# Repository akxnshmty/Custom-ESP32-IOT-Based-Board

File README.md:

# Custom-ESP32-IOT-Based-Board
Custom Multi-Sensor IoT Board with SD Card, Flash Memory, Microphone & High-Speed Routing

This project is a fully custom 4-layer IoT development board built around the ESP32, integrating multiple peripherals such as an SD card interface, external flash memory, I²C sensors, and an onboard microphone. It is designed as a compact, enclosure-ready hardware platform suitable for embedded, IoT, and data-logging applications.

⸻

🚀 Features
	•	ESP32-WROOM based core controller
	•	SD Card interface for data logging
	•	Flash memory IC for additional storage
	•	On-board microphone for audio input
	•	I²C sensor interface for environmental/IMU sensors
	•	User GPIO headers for expansion
	•	4-layer PCB with dedicated ground and power planes
	•	Mounting holes for enclosure integration
	•	Custom 3D models for accurate visualization
	•	Manual routing (0% autorouter) for full design control

⸻

🧩 Hardware Overview

4-Layer Stackup
	•	Layer 1 (Top): Components + High-speed signal routing
	•	Layer 2: Solid GND plane for low-noise return paths
	•	Layer 3: Power plane (5V + 3.3V distribution)
	•	Layer 4 (Bottom): Signal routing + copper zones

This architecture improves signal integrity, noise immunity, and routing efficiency, especially for the SD card, flash memory, and microphone circuits.

⸻

🔧 Key Technical Highlights

Manual Routing
	•	Differential pair routing
	•	Length matching for timing-critical nets
	•	I²C bus routing for sensors
	•	High-speed clock lines
	•	Optimized power traces
	•	Dedicated copper zones for GND and power
	•	Via stitching for ground reinforcement

Design & Validation
	•	Full manual DRC debugging
	•	Fixed annular ring and clearance violations
	•	Added test points, accessible GPIO, and labeled connectors
	•	Optimized analog routing for microphone stage

Mechanical Integration
	•	Exported STEP and WRL models
	•	Assembled 3D view for enclosure planning
	•	Added mounting holes
	•	Custom silkscreen signature

Firmware (Coming Soon)
	•	SD card logging demo
	•	Sensor reading script (I²C)
	•	Microphone input test
	•	Wi-Fi provisioning & OTA updates

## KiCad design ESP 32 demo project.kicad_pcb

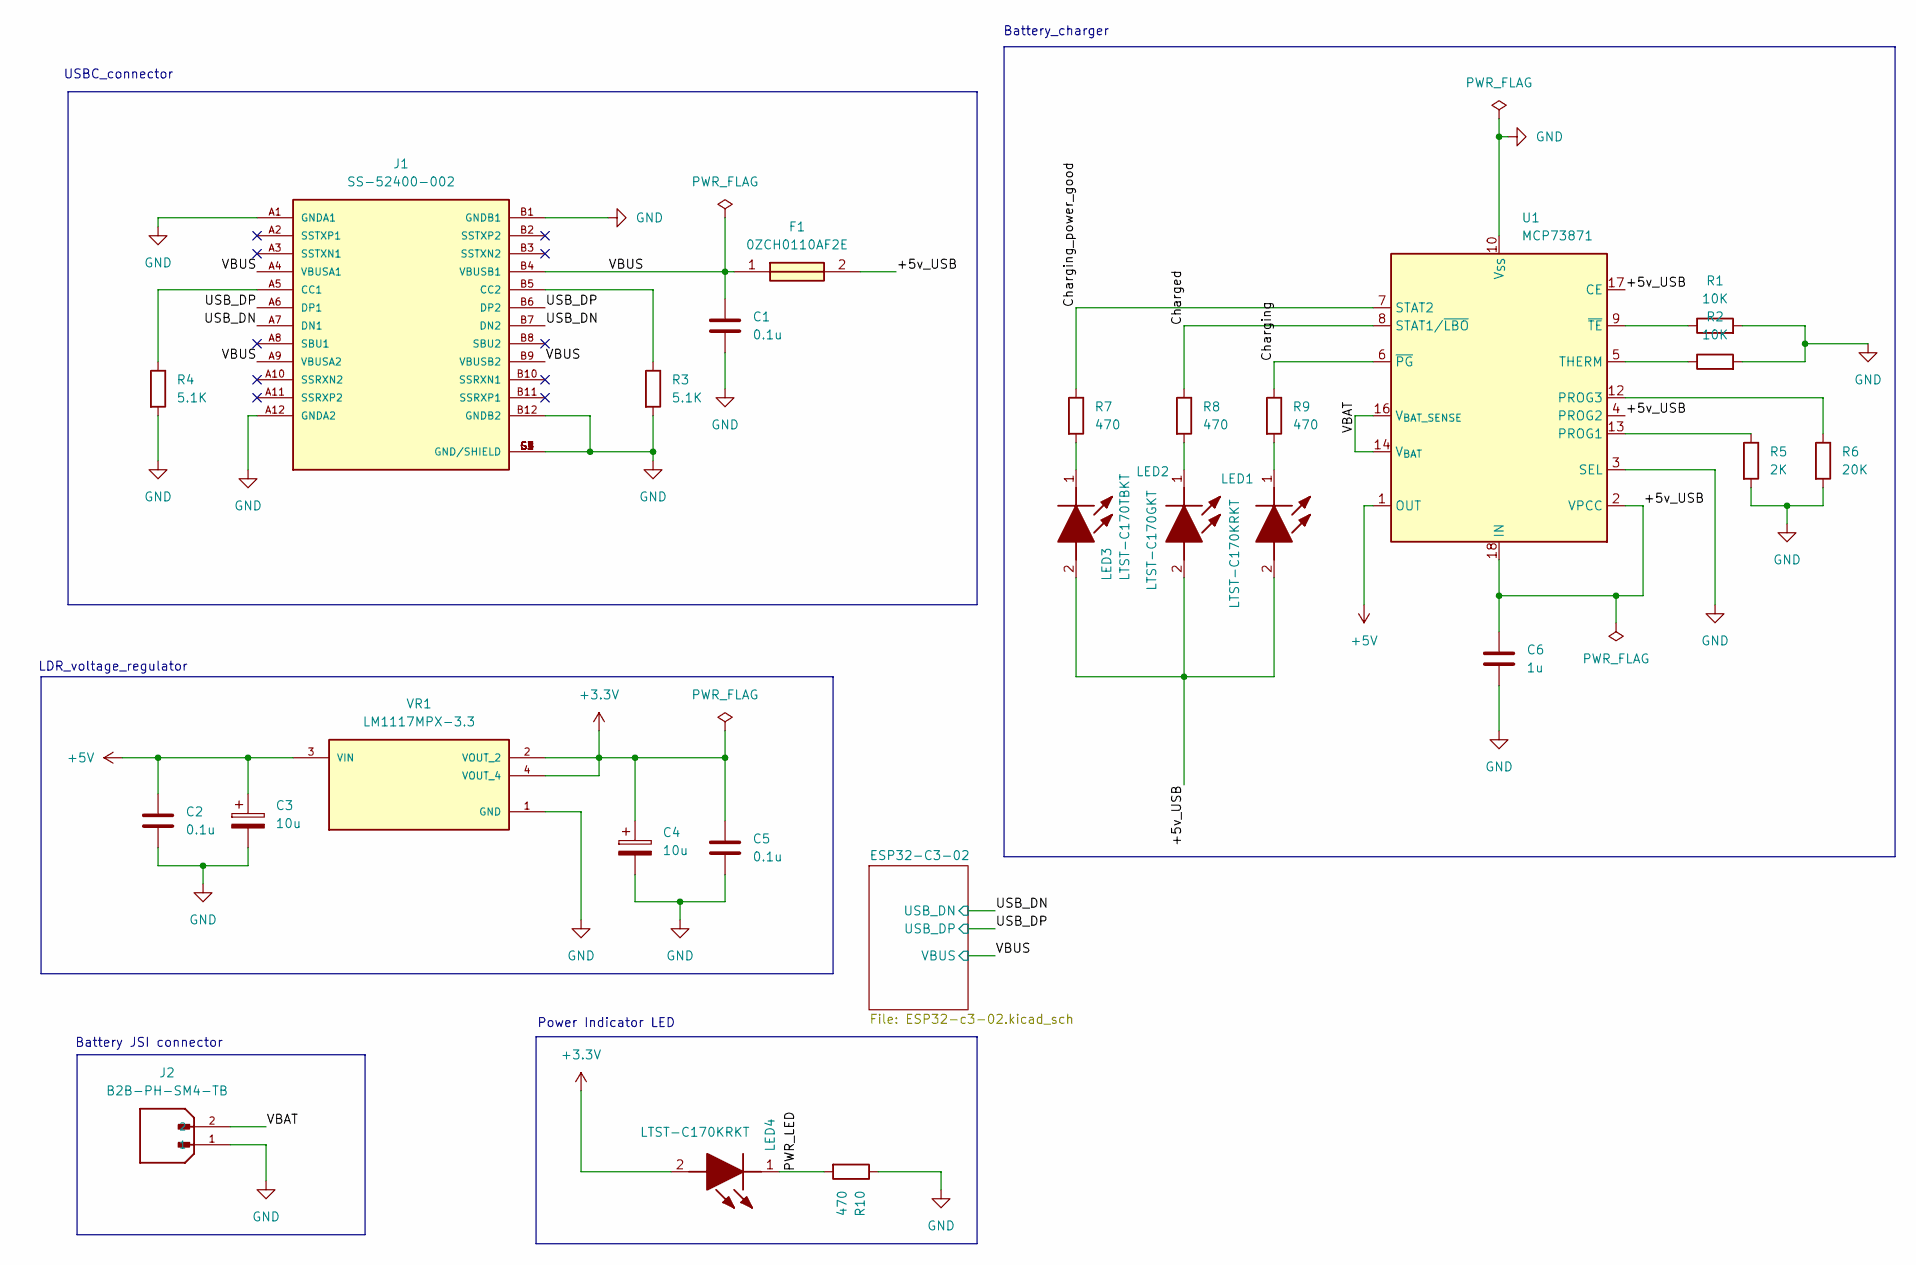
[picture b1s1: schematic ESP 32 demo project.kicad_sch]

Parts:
C1, C2, C5: 0.1u; C_0805_2012Metric
C3, C4: 10u; T491A
C6: 1u; C_0805_2012Metric
F1: 0ZCH0110AF2E; FUSC3226X100N; Manufacturer_Part_Number 0ZCH0110AF2E
J1: SS-52400-002; BELFUSE_SS-52400-002; PARTREV A0
J2: B2B-PH-SM4-TB; JST_B2B-PH-SM4-TB; PARTREV N/A
LED1, LED4: LTST-C170KRKT; LEDC2012X120N; Manufacturer_Part_Number LTST-C170KRKT; Mouser Part Number 859-LTST-C170KRKT
LED2: LTST-C170GKT; LEDC2012X120N; Manufacturer_Part_Number LTST-C170GKT; Mouser Part Number 859-LTST-C170GKT
LED3: LTST-C170TBKT; LEDC2012X120N; Manufacturer_Part_Number LTST-C170TBKT; Mouser Part Number 859-LTST-C170TBKT
R1, R2: 10K; R_0805_2012Metric
R3, R4: 5.1K; R_0805_2012Metric
R5: 2K; R_0805_2012Metric
R6: 20K; R_0805_2012Metric
R7, R8, R9, R10: 470; R_0805_2012Metric
U1: MCP73871; QFN-20-1EP_4x4mm_P0.5mm_EP2.5x2.5mm
VR1: LM1117MPX-3.3; VREG_LM1117MPX-3.3

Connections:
+3.3V: C4.1, C5.1, LED4.2 (A), VR1.2 (VOUT_2), VR1.4 (VOUT_4); also elsewhere on the board
/Charged: R8.1, U1.8 (STAT1/~LBO)
/Charging: R9.1, U1.6 (~PG)
/Charging_power_good: R7.1, U1.7 (STAT2)
/PWR_LED: LED4.1 (K), R10.2; also elsewhere on the board
/USB_DN: J1.A7 (DN1), J1.B7 (DN2); also elsewhere on the board
/USB_DP: J1.A6 (DP1), J1.B6 (DP2); also elsewhere on the board
/VBAT: J2.2, U1.14 (V_{BAT}), U1.15 (V_{BAT}), U1.16 (V_{BAT_SENSE})
/VBUS: C1.1, F1.1, J1.A4 (VBUSA1), J1.A9 (VBUSA2), J1.B4 (VBUSB1), J1.B9 (VBUSB2); also elsewhere on the board
unnamed: J1.A5 (CC1), R4.1
unnamed: J1.B5 (CC2), R3.1
unnamed: LED1.1 (K), R9.2
unnamed: LED2.1 (K), R8.2
unnamed: LED3.1 (K), R7.2
unnamed: R5.1, U1.13 (PROG1)
unnamed: R6.1, U1.12 (PROG3)
unnamed: R2.1, U1.5 (THERM)
unnamed: R1.1, U1.9 (~TE)

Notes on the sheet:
Battery JSI connector
Power Indicator LED
LDR_voltage_regulator
Battery_charger
USBC_connector

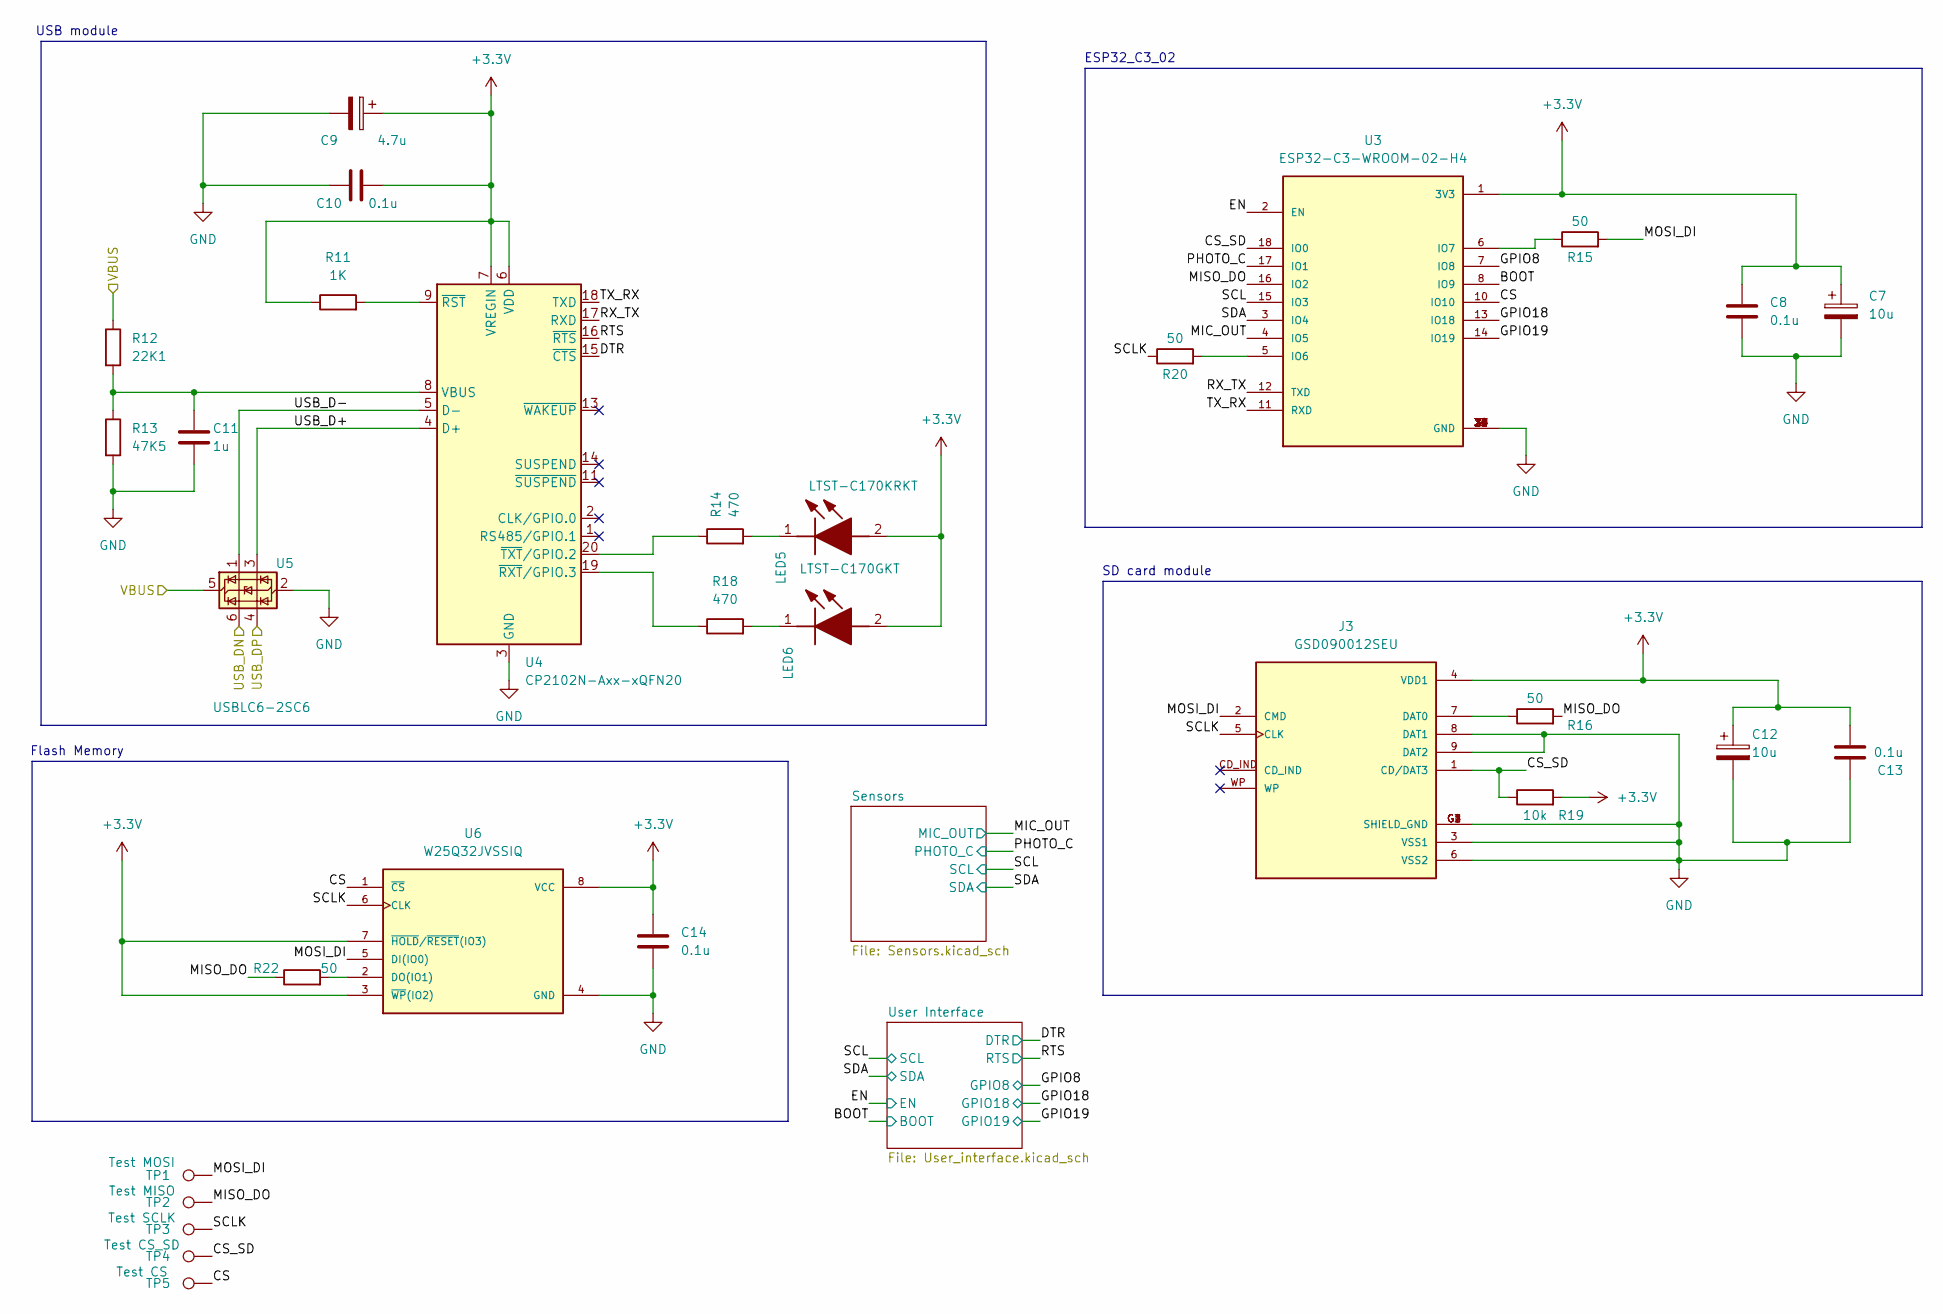
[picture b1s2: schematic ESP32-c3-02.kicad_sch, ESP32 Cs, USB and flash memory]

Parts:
C7, C12: 10u; T491A
C8, C10, C13, C14: 0.1u; C_0805_2012Metric
C9: 4.7u; T491A
C11: 1u; C_0805_2012Metric
J3: GSD090012SEU; AMPHENOL_GSD090012SEU; PARTREV E
LED5: LTST-C170GKT; LEDC2012X120N; Manufacturer_Part_Number LTST-C170GKT; Mouser Part Number 859-LTST-C170GKT
LED6: LTST-C170KRKT; LEDC2012X120N; Manufacturer_Part_Number LTST-C170KRKT; Mouser Part Number 859-LTST-C170KRKT
R11: 1K; R_0805_2012Metric
R12: 22K1; R_0805_2012Metric
R13: 47K5; R_0805_2012Metric
R14, R18: 470; R_0805_2012Metric
R15, R16, R20, R22: 50; R_0805_2012Metric
R19: 10k; R_0805_2012Metric
TP1: Test MOSI; TestPoint_Pad_D1.0mm
TP2: Test MISO; TestPoint_Pad_D1.0mm
TP3: Test SCLK; TestPoint_Pad_D1.0mm
TP4: Test CS_SD; TestPoint_Pad_D1.0mm
TP5: Test CS; TestPoint_Pad_D1.0mm
U3: ESP32-C3-WROOM-02-H4; MODULE_ESP32-C3-WROOM-02-H4
U4: CP2102N-Axx-xQFN20; SiliconLabs_QFN-20-1EP_3x3mm_P0.5mm_EP1.8x1.8mm
U5: USBLC6-2SC6; SOT-23-6
U6: W25Q32JVSSIQ; SOIC127P790X216-8N; M_PART_NUMBER W25QXX

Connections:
+3.3V: C7.1, C8.1, C9.1, C10.1, C12.1, C13.2, C14.1, J3.4 (VDD1), LED5.2 (A), LED6.2 (A), R11.1, R19.2, U3.1 (3V3), U4.6 (VDD), U4.7 (VREGIN), U6.3 (~WP(IO2)), U6.7 (~HOLD/~RESET(IO3)), U6.8 (VCC); also elsewhere on the board
/ESP32-C3-02/BOOT: U3.8 (IO9); also elsewhere on the board
/ESP32-C3-02/CS: TP5.1, U3.10 (IO10), U6.1 (~CS)
/ESP32-C3-02/CS_SD: J3.1 (CD/DAT3), R19.1, TP4.1, U3.18 (IO0)
/ESP32-C3-02/DTR: U4.15 (~CTS); also elsewhere on the board
/ESP32-C3-02/EN: U3.2 (EN); also elsewhere on the board
/ESP32-C3-02/GPIO8: U3.7 (IO8); also elsewhere on the board
/ESP32-C3-02/GPIO18: U3.13 (IO18); also elsewhere on the board
/ESP32-C3-02/GPIO19: U3.14 (IO19); also elsewhere on the board
/ESP32-C3-02/MIC_OUT: U3.4 (IO5); also elsewhere on the board
/ESP32-C3-02/MISO_DO: R16.2, R22.1, TP2.1, U3.16 (IO2)
/ESP32-C3-02/MOSI_DI: J3.2 (CMD), R15.2, TP1.1, U6.5 (DI(IO0))
/ESP32-C3-02/PHOTO_C: U3.17 (IO1); also elsewhere on the board
/ESP32-C3-02/RTS: U4.16 (~RTS); also elsewhere on the board
/ESP32-C3-02/RX_TX: U3.12 (TXD), U4.17 (RXD)
/ESP32-C3-02/SCL: U3.15 (IO3); also elsewhere on the board
/ESP32-C3-02/SCLK: J3.5 (CLK), R20.1, TP3.1, U6.6 (CLK)
/ESP32-C3-02/SDA: U3.3 (IO4); also elsewhere on the board
/ESP32-C3-02/TX_RX: U3.11 (RXD), U4.18 (TXD)
/ESP32-C3-02/USB_D+: U4.4 (D+), U5.3 (I/O2)
/ESP32-C3-02/USB_D-: U4.5 (D-), U5.1 (I/O1)
/USB_DN: U5.6 (I/O1); also elsewhere on the board
/USB_DP: U5.4 (I/O2); also elsewhere on the board
/VBUS: R12.1, U5.5 (VBUS); also elsewhere on the board
unnamed: J3.7 (DAT0), R16.1
unnamed: LED5.1 (K), R14.2
unnamed: LED6.1 (K), R18.2
unnamed: R20.2, U3.5 (IO6)
unnamed: R15.1, U3.6 (IO7)
unnamed: C11.1, R12.2, R13.1, U4.8 (VBUS)
unnamed: R11.2, U4.9 (~RST)
unnamed: R18.1, U4.19 (~RXT/GPIO.3)
unnamed: R14.1, U4.20 (~TXT/GPIO.2)
unnamed: R22.2, U6.2 (DO(IO1))

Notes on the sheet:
Flash Memory
ESP32_C3_02
SD card module
USB module

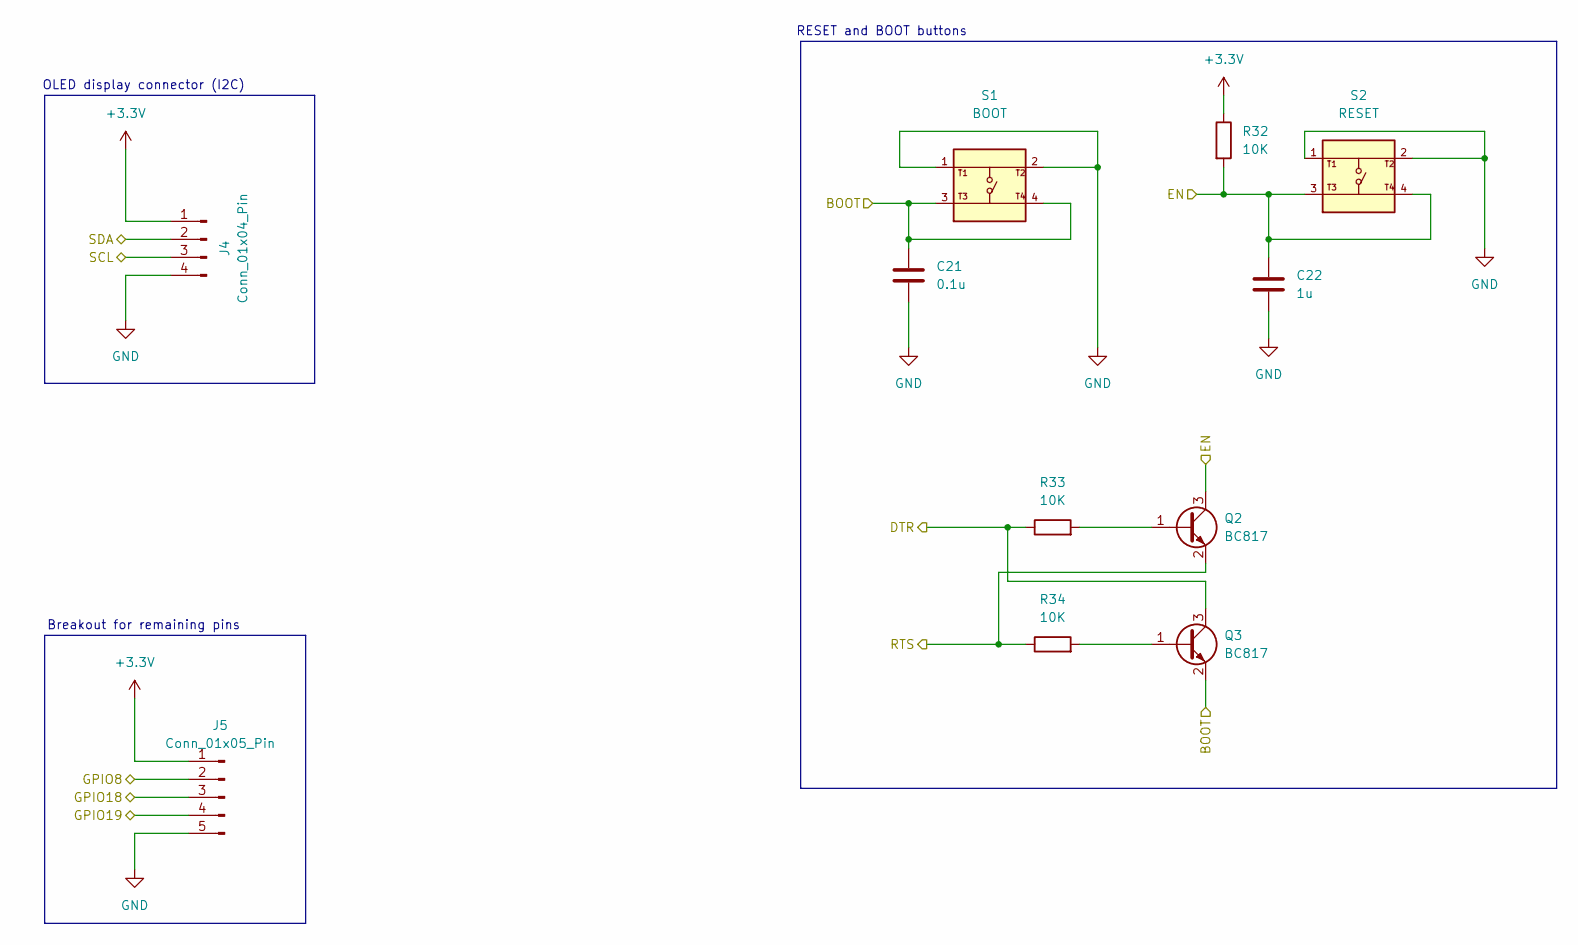
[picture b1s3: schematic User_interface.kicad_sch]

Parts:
C21: 0.1u; C_0805_2012Metric
C22: 1u; C_0805_2012Metric
J4: Conn_01x04_Pin; PinHeader_1x04_P2.54mm_Vertical
J5: Conn_01x05_Pin; PinHeader_1x05_P2.54mm_Vertical
Q2, Q3: BC817; SOT-23
R32, R33, R34: 10K; R_0805_2012Metric
S1: BOOT; SW_USLPT2819DT2TR; PARTREV P
S2: RESET; SW_USLPT2819DT2TR; PARTREV P

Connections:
+3.3V: J4.1, J5.1, R32.1; also elsewhere on the board
/ESP32-C3-02/BOOT: C21.1, Q3.2 (E), S1.3, S1.4; also elsewhere on the board
/ESP32-C3-02/DTR: Q3.3 (C), R33.1; also elsewhere on the board
/ESP32-C3-02/EN: C22.1, Q2.3 (C), R32.2, S2.3, S2.4; also elsewhere on the board
/ESP32-C3-02/GPIO8: J5.2; also elsewhere on the board
/ESP32-C3-02/GPIO18: J5.3; also elsewhere on the board
/ESP32-C3-02/GPIO19: J5.4; also elsewhere on the board
/ESP32-C3-02/RTS: Q2.2 (E), R34.1; also elsewhere on the board
/ESP32-C3-02/SCL: J4.3; also elsewhere on the board
/ESP32-C3-02/SDA: J4.2; also elsewhere on the board
unnamed: Q2.1 (B), R33.2
unnamed: Q3.1 (B), R34.2

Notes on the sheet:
RESET and BOOT buttons
OLED display connector (I2C)
Breakout for remaining pins

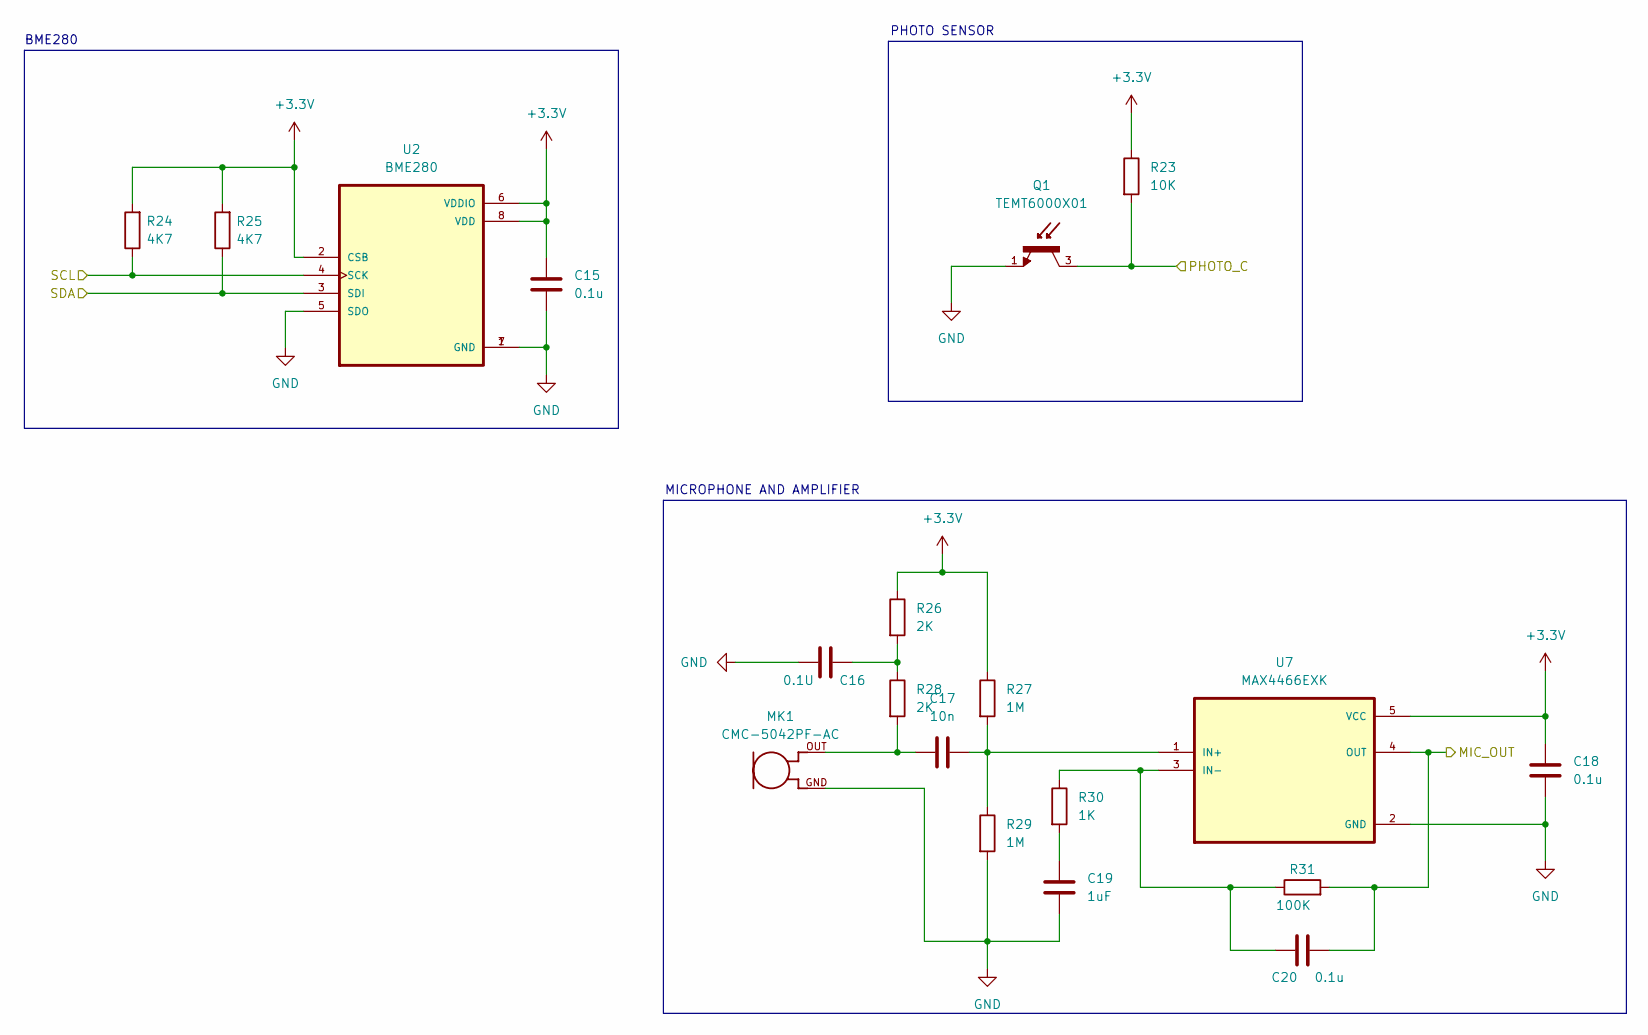
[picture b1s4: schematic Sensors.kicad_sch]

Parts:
C15, C18, C20: 0.1u; C_0805_2012Metric
C16: 0.1U; C_0805_2012Metric
C17: 10n; C_0805_2012Metric
C19: 1uF; C_0805_2012Metric
MK1: CMC-5042PF-AC; CUI_CMC-5042PF-AC
Q1: TEMT6000X01; TRANS_TEMT6000X01; PARTREV 1.9
R23: 10K; R_0805_2012Metric
R24, R25: 4K7; R_0805_2012Metric
R26, R28: 2K; R_0805_2012Metric
R27, R29: 1M; R_0805_2012Metric
R30: 1K; R_0805_2012Metric
R31: 100K; R_0805_2012Metric
U2: BME280; PSON65P250X250X100-8N
U7: MAX4466EXK; SOT65P210X110-5N

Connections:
+3.3V: C15.1, C18.1, R23.1, R24.2, R25.2, R26.1, R27.1, U2.2 (CSB), U2.6 (VDDIO), U2.8 (VDD), U7.5 (VCC); also elsewhere on the board
/ESP32-C3-02/MIC_OUT: C20.2, R31.2, U7.4 (OUT); also elsewhere on the board
/ESP32-C3-02/PHOTO_C: Q1.3, R23.2; also elsewhere on the board
/ESP32-C3-02/SCL: R24.1, U2.4 (SCK); also elsewhere on the board
/ESP32-C3-02/SDA: R25.1, U2.3 (SDI); also elsewhere on the board
unnamed: C16.2, R26.2, R28.1
unnamed: C17.1, MK1.OUT, R28.2
unnamed 31: C19.1, R30.2; also elsewhere on the board
unnamed: C17.2, R27.2, R29.1, U7.1 (IN+)
unnamed: C20.1, R30.1, R31.1, U7.3 (IN-)

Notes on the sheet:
MICROPHONE AND AMPLIFIER
BME280
PHOTO SENSOR

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
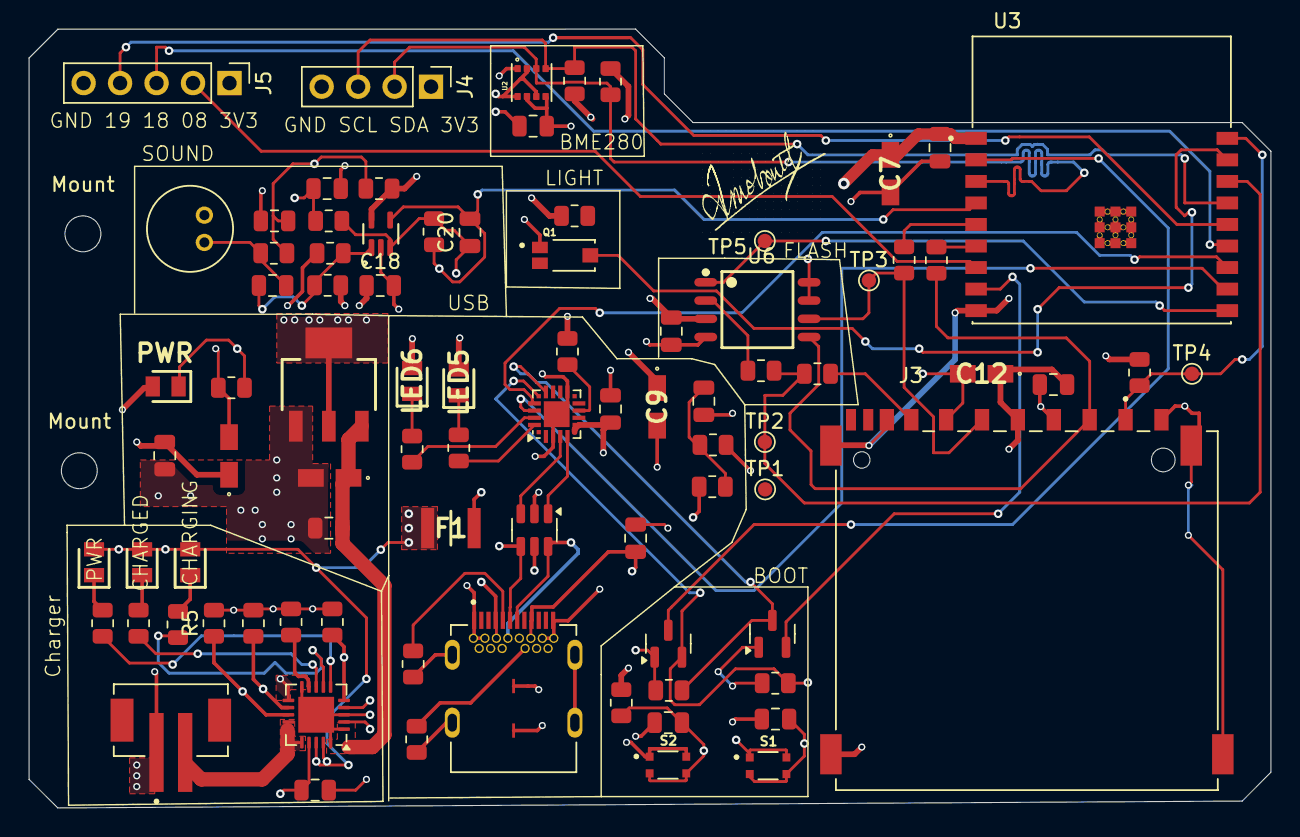
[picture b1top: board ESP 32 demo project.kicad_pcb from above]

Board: 4 copper layers, 86.5 x 54.3 mm, 87 parts (0 on the bottom side), 58 nets.

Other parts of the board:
C: 1uF; C_0805_2012Metric
Mount: MountingHole_2.5mm
Mount#2: MountingHole_2.5mm
PWR: LTST-C170KRKT; LEDC2012X120N

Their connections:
+3.3V: PWR.2 (A); also elsewhere on the board
/PWR_LED: PWR.1 (K); also elsewhere on the board
unnamed 31: C.1; also elsewhere on the board

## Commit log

2025-11-13 Enhance README with project details and features
    Added detailed project description, features, hardware overview, technical highlights, and firmware plans to README.
